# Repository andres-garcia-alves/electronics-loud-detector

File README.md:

# Loud Detector

A loud detector based on ATtiny85.  
Sensitivity threshold and buzzer volume can be configured through trimmers.  
Schematics diagram + PCB diagram (KiCAD 9) and case 3D model (Blender) are also provided.  

&nbsp;

### Features & Notes:

- Sound detection via peak-to-peak window (robust)
- Sensitivity (threshold) via RV1 ADC
- Volume is 100% analog (RV2 in series with buzzer)
- Buzzer + LED share PB1 (digital ON/OFF)
- Mic power gating via PB0 (high-side PNP typical => logic inverted)
- Power input: 18650 battery

&nbsp;

### List of Materials

- 1 x ATtiny85 IC
- 1 x KY-037 Audio sensor module
- 1 x BJT Transistor BC547
- 1 x BJT Transistor BC557
- 1 x 10k ohms trimmer
- 1 x 500 ohms trimmer
- 2 x LED (yellow + red)
- 1 x Buzzer (pasive)
- 1 x Resistor 470 ohms
- 1 x Resistor 1k ohms
- 1 x Resistor 10k ohms
- 2 x Resistor 2k ohms
- 1 x Resistor 100k ohms
- 1 x Capacitor 100 uF (electrolitic)
- 1 x Capacitor 10 uF
- 1 x Rocker Button (power on/off)
- 1 x MT3608 DC/DC Step-Up Converter Module
- 2 x Bornier connector 2-pins / 2 x JST connector 2-pins
- 2 x Header connector 2-pins
- 1 x 18650 battery
- 1 x 18650 battery holder
- Wires

&nbsp;

### Screenshots

| Breadboard                                           | Assembly                                             |
|------------------------------------------------------|------------------------------------------------------|
|                      |                        |

| Schematics Diagram                                   | PCB Layout                                           |
|------------------------------------------------------|------------------------------------------------------|
|              |                      |

| PCB Render 3D                                        | PCB Render 3D                                        |
|------------------------------------------------------|------------------------------------------------------|
|             |            |

| Case 3D Model                                        | Project Final                                        |
|------------------------------------------------------|------------------------------------------------------|
|                   |                |

| Project Final                                        | Project Final                                        |
|------------------------------------------------------|------------------------------------------------------|
|                |                |

See 'Resources' folder for more pictures & videos of the project.

&nbsp;

### Version History

v1.0 (2026.01.24) - Adding schematics, PCB layout and base firmware.  
v1.1 (2026.01.25) - Update firmware: adding 'low-power' feature.  
v1.2 (2026.01.27) - Adding case 3D model.  
v1.3 (2026.01.31) - PCB minor improvements.  
v1.4 (2026.02.02) - Case 3D model minor improvements.  
v1.5 (2026.02.12) - Case 3D model minor improvements, update 'README.md'.  

&nbsp;

This source code is licensed under GPL v3.0  
Please send me your feedback about this project: andres.garcia.alves@gmail.com

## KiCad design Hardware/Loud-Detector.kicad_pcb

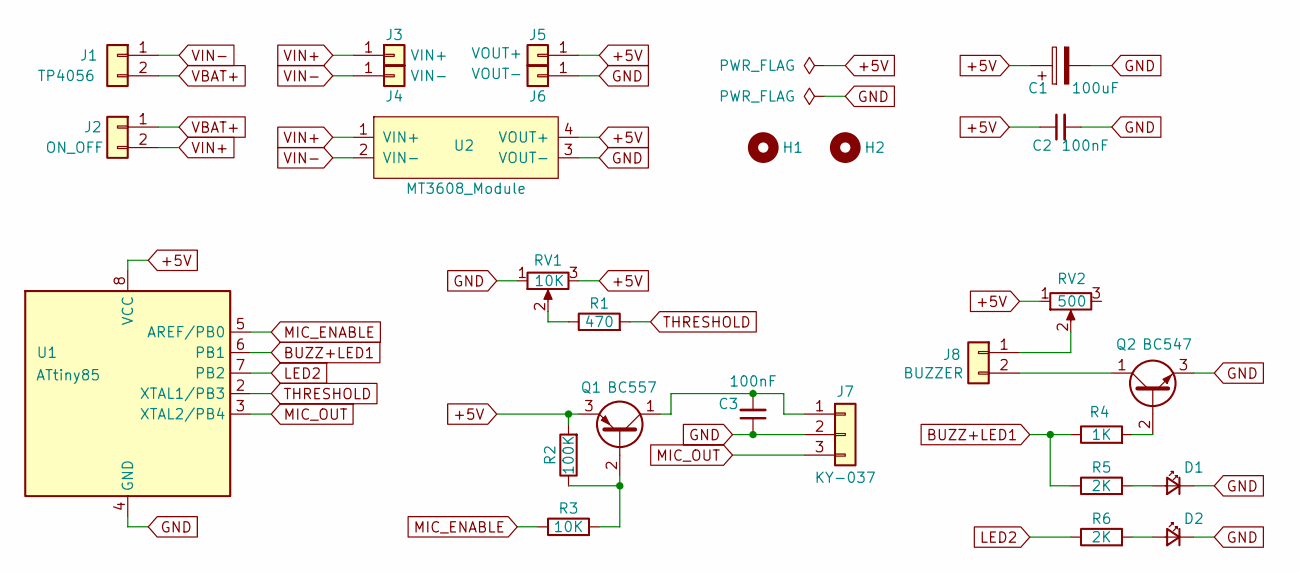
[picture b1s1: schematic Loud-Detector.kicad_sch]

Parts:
C1: 100uF; CP_Radial_D8.0mm_P3.80mm
C2, C3: 100nF; C_Disc_D6.0mm_W2.5mm_P5.00mm; Voltage 1kV; Tolerance 100%
D1, D2: LED; LED_D3.0mm_Horizontal_O3.81mm_Z6.0mm
H1, H2: MountingHole; MountingHole_2.2mm_M2_ISO7380
J1: TP4056; JST_EH_B2B-EH-A_1x02_P2.50mm_Vertical
J2: ON_OFF; JST_EH_B2B-EH-A_1x02_P2.50mm_Vertical
J3: VIN+; PinHeader_1x01_P2.54mm_Vertical
J4: VIN-; PinHeader_1x01_P2.54mm_Vertical
J5: VOUT+; PinHeader_1x01_P2.54mm_Vertical
J6: VOUT-; PinHeader_1x01_P2.54mm_Vertical
J7: KY-037; JST_EH_B3B-EH-A_1x03_P2.50mm_Vertical
J8: BUZZER; JST_EH_B2B-EH-A_1x02_P2.50mm_Vertical
Q1: BC557; TO-92_Inline_Wide
Q2: BC547; TO-92_Inline_Wide
R1: 470; R_Axial_DIN0207_L6.3mm_D2.5mm_P2.54mm_Vertical
R2: 100K; R_Axial_DIN0207_L6.3mm_D2.5mm_P2.54mm_Vertical
R3: 10K; R_Axial_DIN0207_L6.3mm_D2.5mm_P7.62mm_Horizontal
R4: 1K; R_Axial_DIN0207_L6.3mm_D2.5mm_P7.62mm_Horizontal
R5, R6: 2K; R_Axial_DIN0207_L6.3mm_D2.5mm_P2.54mm_Vertical
RV1: 10K; Trimmer_Piher_PT10-V10_Vertical
RV2: 500; Trimmer_Piher_PT10-V10_Vertical
U1: ATtiny85; DIP-8_W7.62mm
U2: MT3608_Module; DC_Boost_Converter_MT3608_Module

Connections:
+5V: C1.1, C2.1, J5.1, Q1.3 (E), R2.2, RV1.3, RV2.1, U1.8 (VCC), U2.4 (VOUT+)
BUZZ+LED1: R4.1, R5.1, U1.6 (PB1)
GND: C1.2, C2.2, C3.1, D1.1 (K), D2.1 (K), J6.1, J7.2, Q2.3 (E), RV1.1, U1.4 (GND), U2.3 (VOUT-)
LED2: R6.1, U1.7 (PB2)
MIC_ENABLE: R3.1, U1.5 (AREF/PB0)
MIC_OUT: J7.3, U1.3 (XTAL2/PB4)
unnamed: D1.2 (A), R5.2
unnamed: D2.2 (A), R6.2
unnamed: C3.2, J7.1, Q1.1 (C)
unnamed: J8.1, RV2.2
unnamed: J8.2, Q2.1 (C)
unnamed: Q1.2 (B), R2.1, R3.2
unnamed: Q2.2 (B), R4.2
unnamed: R1.1, RV1.2
THRESHOLD: R1.2, U1.2 (XTAL1/PB3)
VBAT+: J1.2, J2.1
VIN+: J2.2, J3.1, U2.1 (VIN+)
VIN-: J1.1, J4.1, U2.2 (VIN-)

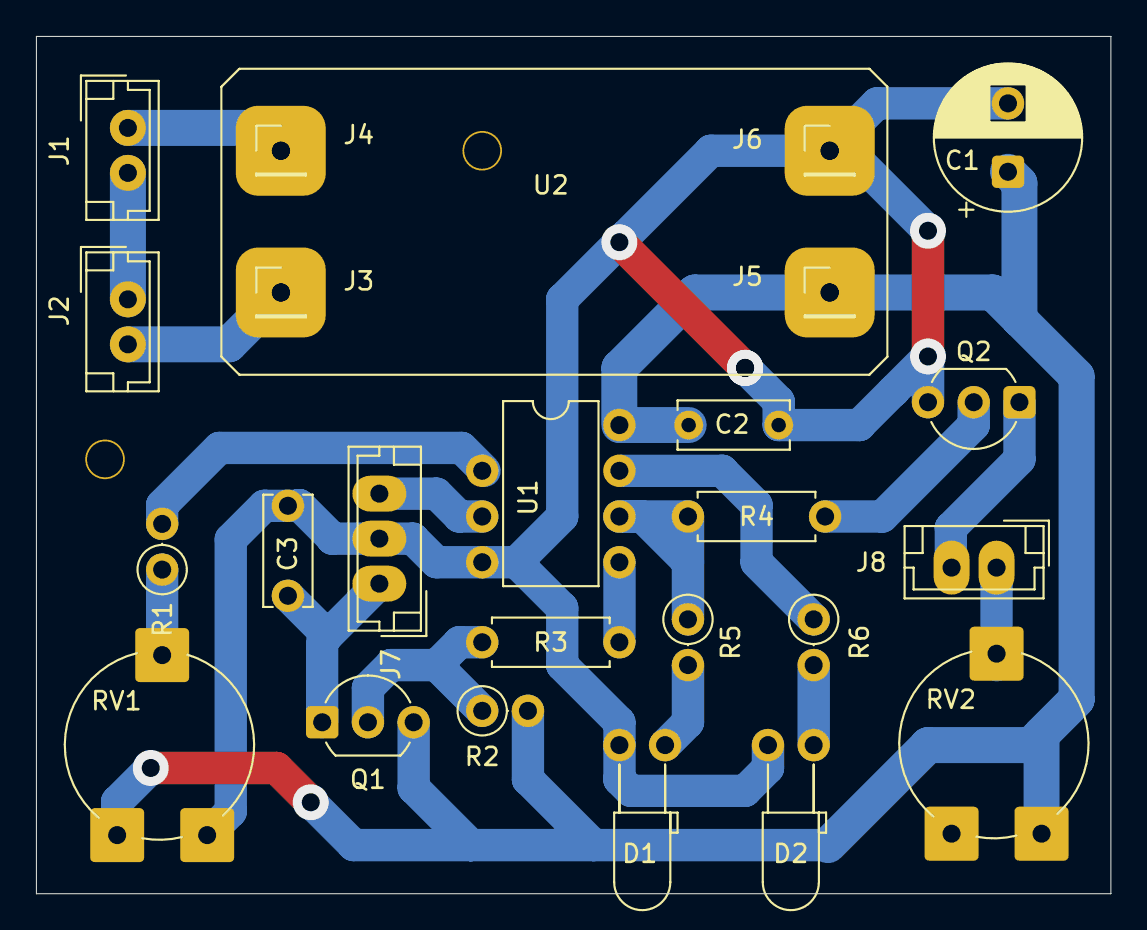
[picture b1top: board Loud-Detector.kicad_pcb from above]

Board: 2 copper layers, 59.7 x 47.6 mm, 27 parts (0 on the bottom side), 18 nets.

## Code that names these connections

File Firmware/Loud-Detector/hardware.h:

#pragma once

// pin mapping (ATtiny85)
#define PIN_MIC_ENABLE    PB0     // PB0 -> Controls Q1 high-side
#define PIN_BUZZ_LED      PB1     // PB1 -> Q2 base + LED1
#define PIN_LED2          PB2     // PB2 -> LED2

#define PIN_MIC_ADC       A2      // PB4 (ADC2) -> KY-038 sensor (pin AO)
#define PIN_THR_ADC       A3      // PB3 (ADC3) -> RV1 sensitivity control

// inverse logic (Q1: BC557)
#define MIC_ON            LOW
#define MIC_OFF           HIGH

// audio sensor parameters (KY-037/KY-038)
#define SENSOR_WARMUP_MS  20UL    // 20 ms
#define SENSOR_WINDOW_MS  40UL    // 40 ms

// threshold mapping (RV1 -> peak-to-peak threshold)
//#define THR_MIN_P2P       8       // very sensitive
//#define THR_MAX_P2P       220     // very strict
#define THR_MIN_ENERGY    2//5
#define THR_MAX_ENERGY    30//60

// variables + enums
enum LoudLevel {LEVEL1, LEVEL2};

// funtions declaration + inline functions
void inline micPowerOn()  { digitalWrite(PIN_MIC_ENABLE, MIC_ON); delay(SENSOR_WARMUP_MS); }
void inline micPowerOff() { digitalWrite(PIN_MIC_ENABLE, MIC_OFF); }


// module initialization
void hardwareInit()
{
  pinMode(PIN_MIC_ENABLE, OUTPUT);
  pinMode(PIN_MIC_ADC, INPUT);
  pinMode(PIN_THR_ADC, INPUT);
  pinMode(PIN_BUZZ_LED, OUTPUT);
  pinMode(PIN_LED2, OUTPUT);

  micPowerOff();
  digitalWrite(PIN_BUZZ_LED, LOW);
  digitalWrite(PIN_LED2, LOW);
}


void buzzStart(LoudLevel loudLevel)
{
  // digital ON (volume handled by analog trimmer RV2)
  tone(PIN_BUZZ_LED, 2000);   // 2 Khz

  if (loudLevel == LEVEL2) { digitalWrite(PIN_LED2, HIGH); }
}

void buzzStop()
{
  noTone(PIN_BUZZ_LED);
  digitalWrite(PIN_LED2, LOW);
}

int micMeasureEnergy()
{
  unsigned long start = millis();
  long sum = 0;
  int samples = 0;

  // Primero estimamos el nivel medio
  long mean = 0;
  int count = 0;

  while (millis() - start < SENSOR_WINDOW_MS)
  {
    int value = analogRead(PIN_MIC_ADC);
    mean += value;
    count++;
  }

  mean /= count;

  // Segunda pasada: energía absoluta
  start = millis();
  while (millis() - start < SENSOR_WINDOW_MS)
  {
    int value = analogRead(PIN_MIC_ADC);
    sum += abs(value - mean);
    samples++;
  }

  return sum / samples;  // energía promedio
}

/*int micMeasurePeakToPeak()
{
  int minRaw = 1023;
  int maxRaw = 0;
  unsigned long start = millis();

  while (millis() - start < SENSOR_WINDOW_MS)
  {
    int value = analogRead(PIN_MIC_ADC);

    if (value < minRaw) { minRaw = value; }
    if (value > maxRaw) { maxRaw = value; }
  }

  return maxRaw - minRaw;
}*/

int adcThresholdEnergy()
{
  int thresholdRaw = analogRead(PIN_THR_ADC);   // 0..1023
  int threshold = map(thresholdRaw, 0, 1023, THR_MIN_ENERGY, THR_MAX_ENERGY);

  if (threshold < THR_MIN_ENERGY) { threshold = THR_MIN_ENERGY; }
  if (threshold > THR_MAX_ENERGY) { threshold = THR_MAX_ENERGY; }

  return threshold;
}

/*int adcThresholdPeakToPeak()
{
  int thresholdRaw = analogRead(PIN_THR_ADC);   // 0..1023
  int threshold = map(thresholdRaw, 0, 1023, THR_MIN_P2P, THR_MAX_P2P);

  // Safety clamp
  if (threshold < THR_MIN_P2P) { threshold = THR_MIN_P2P; }
  if (threshold > THR_MAX_P2P) { threshold = THR_MAX_P2P; }

  return threshold;
}*/

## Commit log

2026-01-24 Adding schematics, PCB layout and base firmware
2026-01-25 Update firmware: adding 'low-power' feature
2026-01-27 Adding case 3D model
2026-01-31 PCB minor improvements
2026-02-02 3D model minor improvements
2026-02-11 Case 3D model minor improvements
2026-02-12 Update 'README.md'
